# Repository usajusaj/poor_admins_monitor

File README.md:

# Poor Admin's Monitor
For my fellow sysadmins who would like to be responsible and monitor server room temperature but professional monitor appliances are too expensive.

The plan here is pretty simple, all you need is:
- Some sort of x86/ARM capable single-board computer like [RaspberryPI](https://www.raspberrypi.org/) with GPIO pins
- A few components, the star of the show is 1-Wire temperature sensor like [MAX31820](https://datasheets.maximintegrated.com/en/ds/MAX31820.pdf)
- Basic soldering experience

## Design
1-Wire ambient temperature sensing devices are cheap (~$1CAD/each), easy to control (1-wire protocol drivers are readily available) and one can chain a lot of them on a single wire. I'm using UTP since every server room has plenty spare.

I'm chose a standalone C++ web framework to avoid running the bloat that are NGINX/Apache2 + Django/PHP/... on an rpi. But deep down I just wanted to try something new.

## Building
- Download/clone Drogon: https://github.com/an-tao/drogon
- Follow its installation steps, before running cmake add this line to drogon's CMakeList.txt to fix linking errors on RaspberryPI
```cmake
target_link_libraries(${PROJECT_NAME} PUBLIC atomic)
```
- Install drogon
- Download/clone this code, do usual
```shell script
$ mkdir build
$ cd build
$ cmake ..
$ make
```

## Running
- initialize database
```shell script
sqlite3 database.db
> .read sqlite3.sql
```
- put [poll_devices.py](poll_devices.py) in a crontab at arbitrary interval, ie every minute:
```shell script
* * * * *       /home/pi/poor_admins_monitor/poll_devices.py /home/pi/poor_admins_monitor/database.db
``` 

- while database is filling up with first data, rename [config.json.template](config.json.template) to config.json and adjust settings to your liking
- run web server with
```shell script
./poor_admins_monitor
``` 

- Point browser to:
  - `http://host:port/api/v1/device/list`
  - `http://host:port/api/v1/device/get/1`
  - `http://host:port/api/v1/device/get/1/history`
  
## Future features
- Advertise service over avahi
- Configuration script to assign each device a verbose name and location
- Add systemd timer example file for a <1m polling interval (impossible in cron)

## Thanks to
- [Drogon](https://github.com/an-tao/drogon) for an awesome C++ web framework
- [Pure.css](https://purecss.io/) for an elegant lightweight css scaffold
- [Chart.js](https://www.chartjs.org/) for slick charts

## Gallery
### Main page with graphed temperatures

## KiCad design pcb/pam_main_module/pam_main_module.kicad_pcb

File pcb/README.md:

# Printed circuit board (PCB) designs
Schemes for convenient small pcb's of the two main components of this project. 
Software used to create and edit this is [KiCad](https://www.kicad-pcb.org/).

Each module can be also soldered by hand on a proto-board or even directly on 
the connector pins, but using a custom pcb is easier.

## [pam_main_module](pam_main_module)
KiCad project for the main module that connects to a single-board device (RPi) 
GPIO pins and then uses a common UTP over RJ45 (aka ethernet) to connect 1-Wire
thermal sensors. Pins used/needed are: +3.3V, GROUND and DATA (digital I/O).
Board is designed with 3 RJ45 connectors so you can route the cables in multiple 
directions, but only one is required to be soldered in place.

## [pam_chain_module](pam_chain_module)
KiCad project for the chain module with thermal sensor. This module features 
2 RJ45 connectors for daisy-chaining them in series. Thermal sensor is soldered 
on the opposite side so that it's not sandwiched between the two RJ45 casings for more
accurate readings.

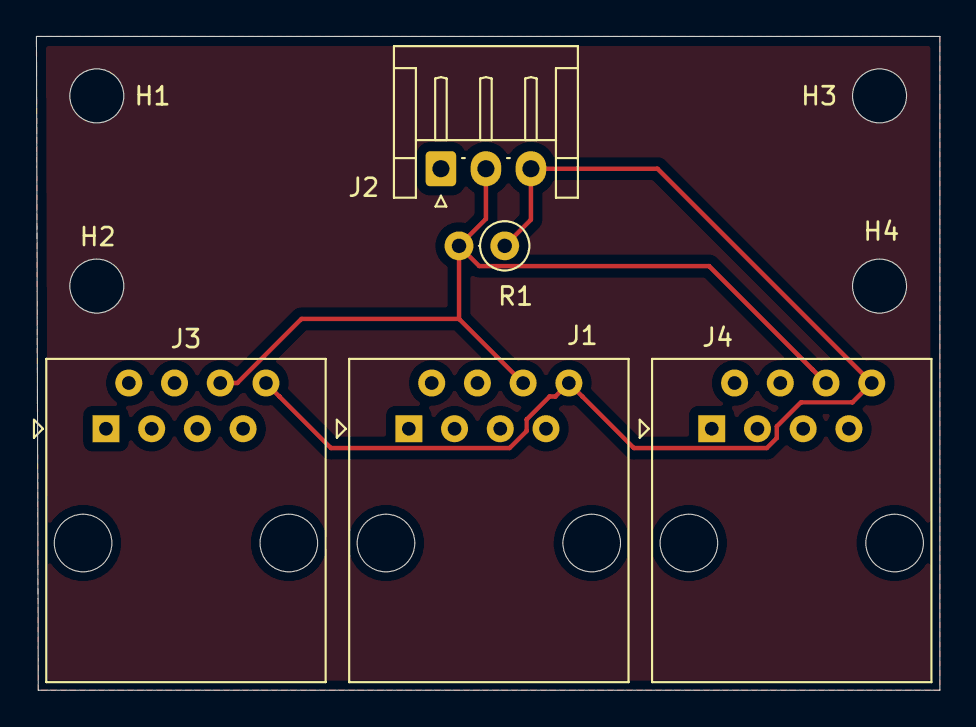
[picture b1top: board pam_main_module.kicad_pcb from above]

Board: 2 copper layers, 50.2 x 36.3 mm, 9 parts (0 on the bottom side), 3 nets.

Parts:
H1, H2, H3, H4: MountingHole; MountingHole_3mm
J1, J3, J4: RJ45; RJ45_Amphenol_54602-x08_Horizontal
J2: 1WCONN; JST_EH_S3B-EH_1x03_P2.50mm_Horizontal
R1: 4.7k; R_Axial_DIN0207_L6.3mm_D2.5mm_P2.54mm_Vertical

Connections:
/DATA: J1.6, J2.2, J3.6, J4.6, R1.2
GND: J1.4, J2.1, J3.4, J4.4
VCC: J1.8, J2.3, J3.8, J4.8, R1.1

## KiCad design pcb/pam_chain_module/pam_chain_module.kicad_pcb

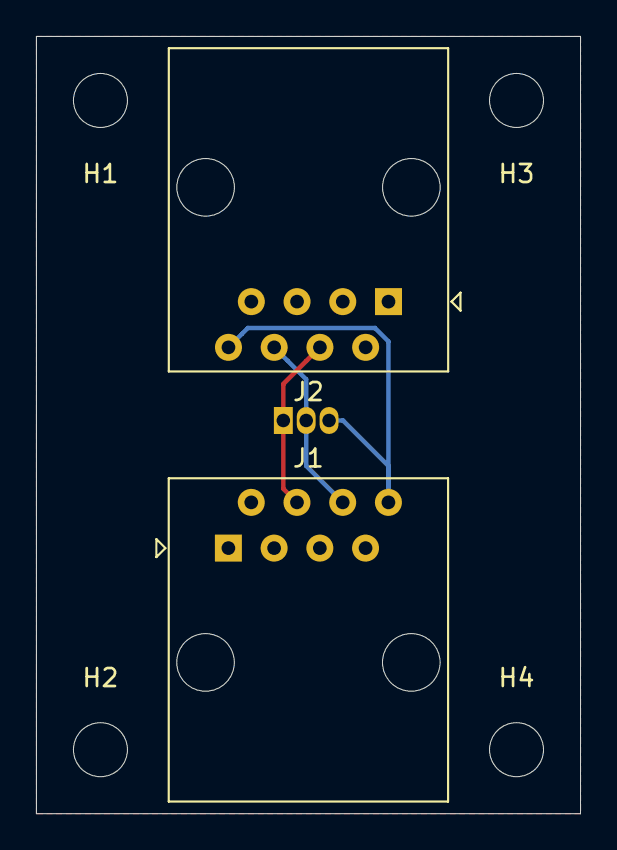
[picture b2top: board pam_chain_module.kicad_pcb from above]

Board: 2 copper layers, 30.2 x 43.2 mm, 7 parts (1 on the bottom side), 3 nets.

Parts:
H1, H2, H3, H4: MountingHole; MountingHole_3mm
J1, J2: RJ45; RJ45_Amphenol_54602-x08_Horizontal
U1: MAX31820; TO-92_Inline

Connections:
/DATA: J1.6, J2.6, U1.2
GND: J1.4, J2.4, U1.1
VCC: J1.8, J2.8, U1.3

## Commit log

2020-04-23 Updated ignores
2020-04-23 Included some useful dirs
2020-04-24 Added device history API, updated README.md
2020-04-24 Fill reading table using trigger instead of inserts
2020-04-25 Simple graphs
2020-04-25 Better main
2020-04-28 Better UI
2020-04-29 Too much to write it all down, good stuff
2020-04-29 Added pcb designs for main and link modules
2020-04-29 Added systemd service file and updated README
2020-04-29 Added readme for pcb designs
2020-04-29 Add gallery
2020-04-30 Update README.md
    Added new TODO feature
2020-04-30 Update README.md
    Added references to key libraries
2020-04-30 Fixed a bug in removeTrack
2020-04-30 Have a consistent device ordering
2020-04-30 Use verbose name if defined
2020-07-18 Added email reporting to polling script
2020-07-18 Modified graph options
2020-07-18 Accidentally commited debug statements
2020-07-18 A few more informative log statements
2020-07-18 Bug in threhold format fixed
2020-07-30 Update issue templates
2020-10-01 Optimized SQL query for history
2020-10-01 Added missing INDEX on reading (device)
2021-02-10 Update poll_devices.py
    Proper handling of verbose_name, even on new devices
